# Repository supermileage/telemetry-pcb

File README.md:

# Telemetry PCB

Printed Circuit Board design for the Supermileage Telemetry Module. More information on its functionality can be found in the [firmware repo](https://github.com/supermileage/telemetry-firmware/tree/master).

The PCB is a 2-layer design, intended to be manufactured with 1oz copper. It was designed to be as small and as versatile as possible, to fit into tight spaces on multiple vehicles. The PCB features:

- Particle Boron Microcontroller with built-in LTE Connection
- LMS6DSO Accelerometer & Gyroscope
- 2x MAX31855K Thermocouple ICs with 2 Thermocouple inputs
- MCP2515 CAN Controller, TCAN332 CAN Transciever, 2x CAN ports
- Switchable TTL UART, RS232 UART (MAX3232), or optical UART (IF-D92)
- Connector for external i2c GPS module
- LEDs and button for monitoring & control

## Schematic Preview

## PCB Preview

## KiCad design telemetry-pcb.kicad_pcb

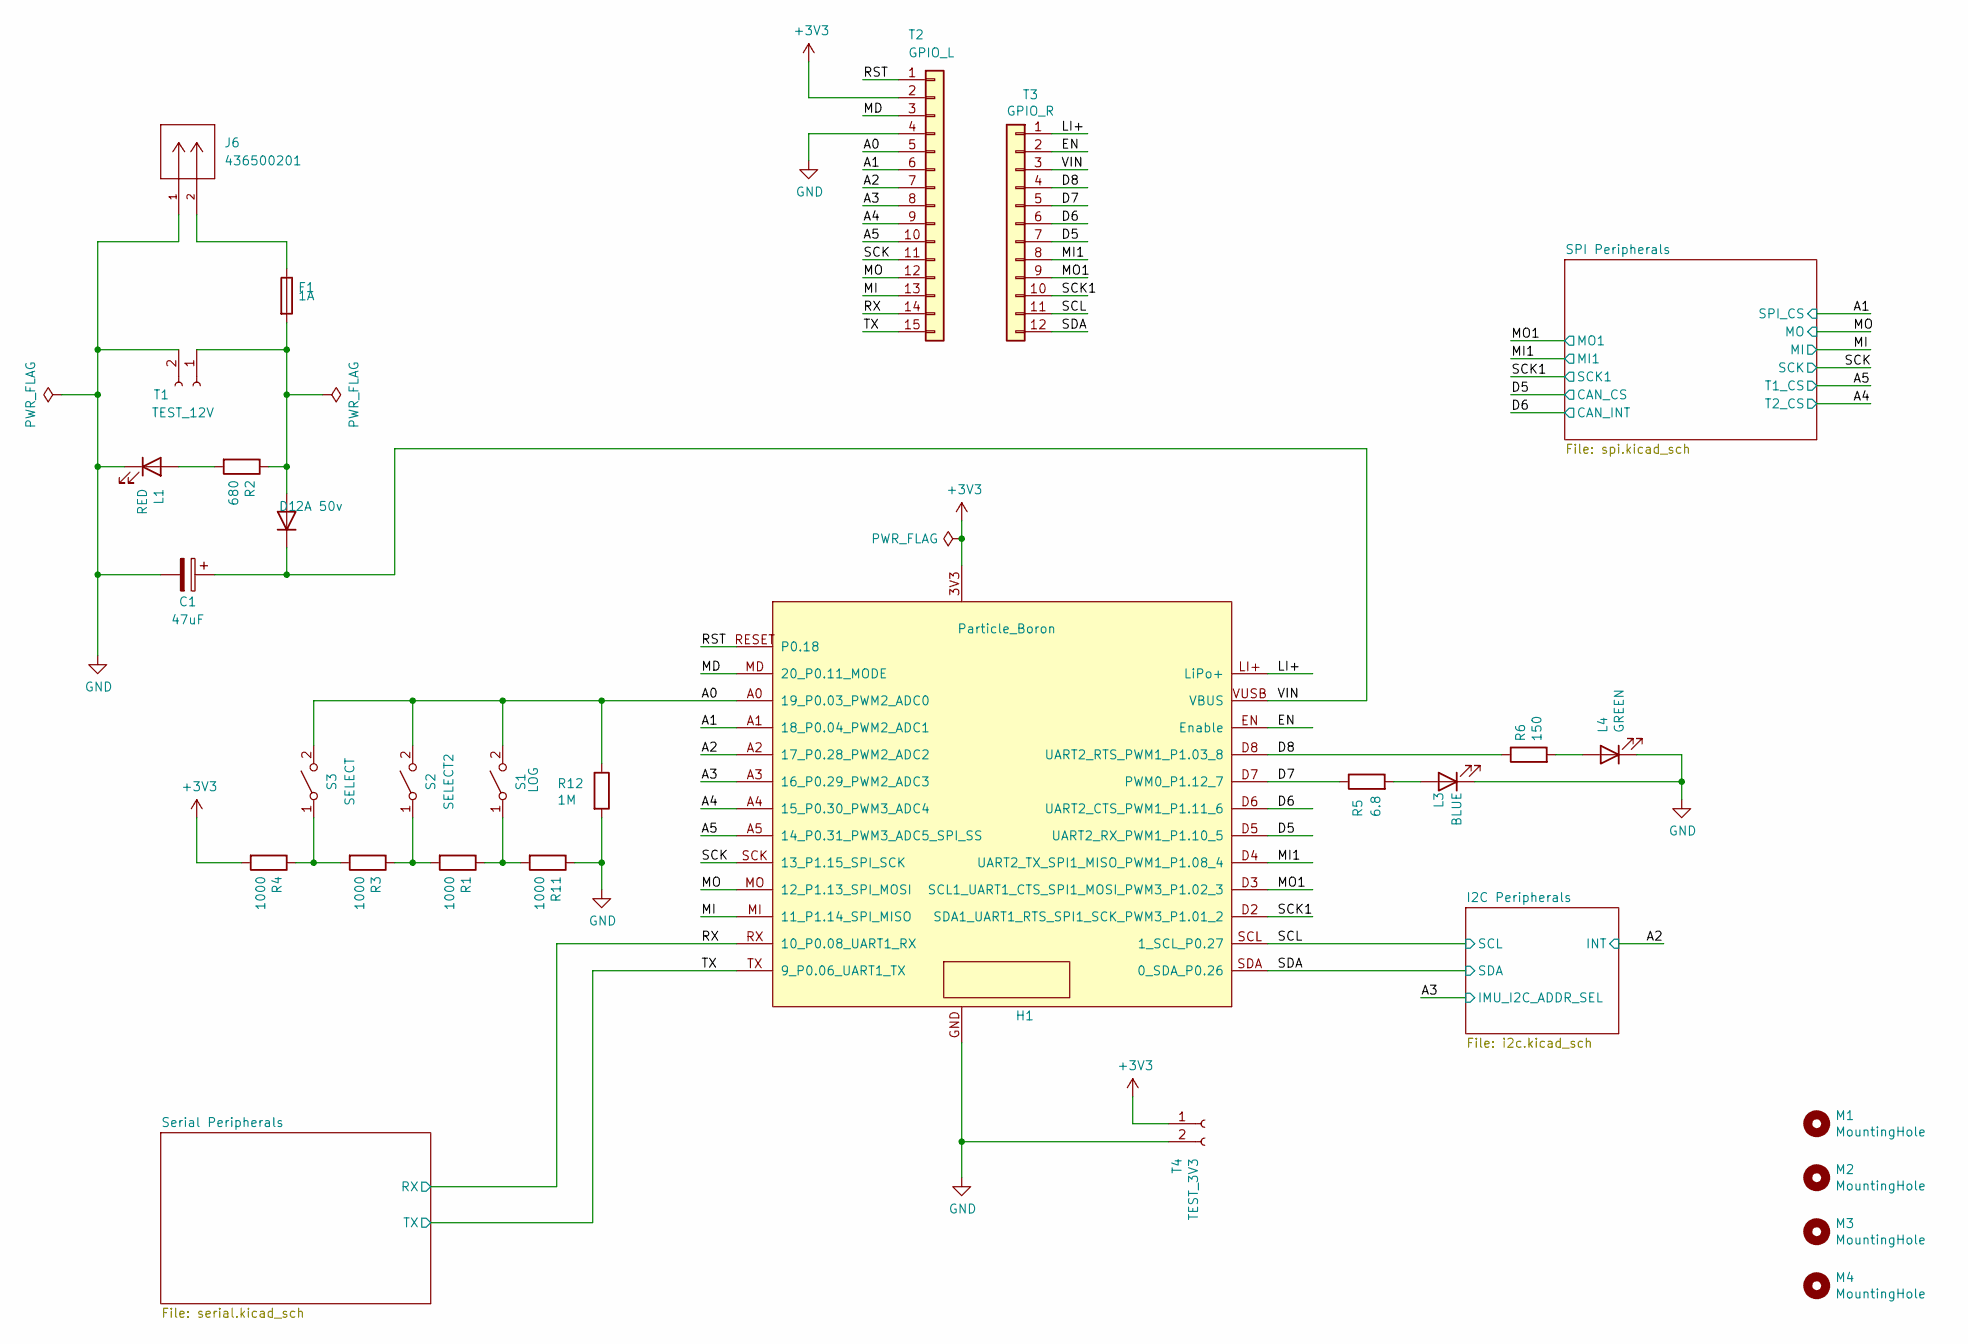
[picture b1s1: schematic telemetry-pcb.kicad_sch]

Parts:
C1: 47uF; CP_Elec_6.3x5.4
D1: 2A 50v; D_SMA
F1: 1A; 0154001.DRL
H1: Particle_Boron; Particle_boron
J6: 436500201; CONN_SD-43650-001_02_MOL; MANUFACTURER_PART_NUMBER 436500201
L1: RED; LED_0805_2012Metric
L3: BLUE; LED_0805_2012Metric
L4: GREEN; LED_0805_2012Metric
M1, M2, M3, M4: MountingHole; MountingHole_3.2mm_M3
R1, R3, R4, R11: 1000; R_0805_2012Metric
R2: 680; R_0805_2012Metric
R5: 6.8; R_0805_2012Metric
R6: 150; R_0805_2012Metric
R12: 1M; R_0805_2012Metric
S1: LOG; SW_PUSH_6mm_H13mm
S2: SELECT2; SW_PUSH_6mm_H13mm
S3: SELECT; SW_PUSH_6mm_H13mm
T1: TEST_12V; TestPoint_2Pads_Pitch2.54mm_Drill0.8mm
T2: GPIO_L; Boron_Pins_L
T3: GPIO_R; Boron_Pins_R
T4: TEST_3V3; TestPoint_2Pads_Pitch2.54mm_Drill0.8mm

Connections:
+3V3: H1.3V3, R4.2, T2.2, T4.1; also elsewhere on the board
/A0: H1.A0 (19_P0.03_PWM2_ADC0), R12.1, S1.2 (B), S2.2 (B), S3.2 (B), T2.5
/A1: H1.A1 (18_P0.04_PWM2_ADC1), T2.6; also elsewhere on the board
/A2: H1.A2 (17_P0.28_PWM2_ADC2), T2.7; also elsewhere on the board
/A3: H1.A3 (16_P0.29_PWM2_ADC3), T2.8; also elsewhere on the board
/A4: H1.A4 (15_P0.30_PWM3_ADC4), T2.9; also elsewhere on the board
/A5: H1.A5 (14_P0.31_PWM3_ADC5_SPI_SS), T2.10; also elsewhere on the board
/D5: H1.D5 (UART2_RX_PWM1_P1.10_5), T3.7; also elsewhere on the board
/D6: H1.D6 (UART2_CTS_PWM1_P1.11_6), T3.6; also elsewhere on the board
/D7: H1.D7 (PWM0_P1.12_7), R5.1, T3.5
/D8: H1.D8 (UART2_RTS_PWM1_P1.03_8), R6.1, T3.4
/EN: H1.EN (Enable), T3.2
/LI+: H1.LI+ (LiPo+), T3.1
/MD: H1.MD (20_P0.11_MODE), T2.3
/MI: H1.MI (11_P1.14_SPI_MISO), T2.13; also elsewhere on the board
/MI1: H1.D4 (UART2_TX_SPI1_MISO_PWM1_P1.08_4), T3.8; also elsewhere on the board
/MO: H1.MO (12_P1.13_SPI_MOSI), T2.12; also elsewhere on the board
/MO1: H1.D3 (SCL1_UART1_CTS_SPI1_MOSI_PWM3_P1.02_3), T3.9; also elsewhere on the board
/RST: H1.RESET (P0.18), T2.1
/RX: H1.RX (10_P0.08_UART1_RX), T2.14; also elsewhere on the board
/SCK: H1.SCK (13_P1.15_SPI_SCK), T2.11; also elsewhere on the board
/SCK1: H1.D2 (SDA1_UART1_RTS_SPI1_SCK_PWM3_P1.01_2), T3.10; also elsewhere on the board
/SCL: H1.SCL (1_SCL_P0.27), T3.11; also elsewhere on the board
/SDA: H1.SDA (0_SDA_P0.26), T3.12; also elsewhere on the board
/TX: H1.TX (9_P0.06_UART1_TX), T2.15; also elsewhere on the board
/VIN: C1.1, D1.1 (K), H1.VUSB (VBUS), T3.3
GND: C1.2, H1.GND, J6.1, L1.1 (K), L3.1 (K), L4.1 (K), R11.1, R12.2, T1.2, T2.4, T4.2; also elsewhere on the board
unnamed: D1.2 (A), F1.2, R2.1, T1.1
unnamed: F1.1, J6.2
unnamed: L1.2 (A), R2.2
unnamed: L3.2 (A), R5.2
unnamed: L4.2 (A), R6.2
unnamed: R1.1, R11.2, S1.1 (A)
unnamed: R1.2, R3.1, S2.1 (A)
unnamed: R3.2, R4.1, S3.1 (A)

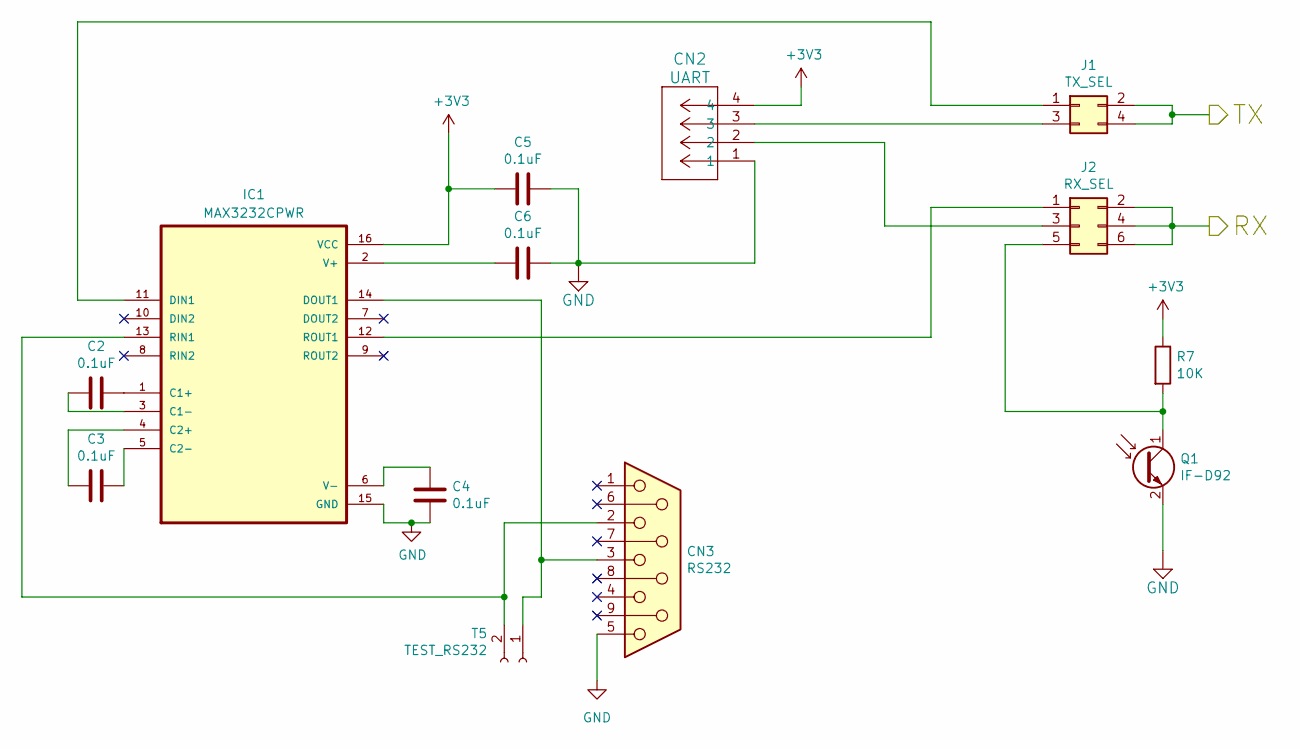
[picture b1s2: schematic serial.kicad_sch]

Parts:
C2, C3, C4, C5, C6: 0.1uF; C_0805_2012Metric
CN2: UART; CONN_SD-43650-001_04_MOL
CN3: RS232; DSUB-9_Female_Horizontal_P2.77x2.84mm_EdgePinOffset7.70mm_H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
IC1: MAX3232CPWR; TSSOP-16_4.4x5mm_P0.65mm
J1: TX_SEL; PinHeader_2x02_P2.54mm_Horizontal
J2: RX_SEL; PinHeader_2x03_P2.54mm_Horizontal
Q1: IF-D92
R7: 10K; R_0805_2012Metric
T5: TEST_RS232; TestPoint_2Pads_Pitch2.54mm_Drill0.8mm

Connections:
+3V3: C5.2, CN2.4, IC1.16 (VCC), R7.1; also elsewhere on the board
/RX: J2.2, J2.4, J2.6; also elsewhere on the board
/Serial Peripherals/RX_232: CN3.2, IC1.13 (RIN1), T5.2
/Serial Peripherals/TX_232: CN3.3, IC1.14 (DOUT1), T5.1
/TX: J1.2, J1.4; also elsewhere on the board
GND: C4.2, C5.1, C6.1, CN2.1, CN3.5, IC1.15 (GND), Q1.2 (E); also elsewhere on the board
unnamed: C2.1, IC1.1 (C1+)
unnamed: C2.2, IC1.3 (C1-)
unnamed: C3.2, IC1.4 (C2+)
unnamed: C3.1, IC1.5 (C2-)
unnamed: IC1.11 (DIN1), J1.1
unnamed: IC1.12 (ROUT1), J2.1
unnamed: C6.2, IC1.2 (V+)
unnamed: C4.1, IC1.6 (V-)
unnamed: CN2.3, J1.3
unnamed: CN2.2, J2.3
unnamed: J2.5, Q1.1 (C), R7.2

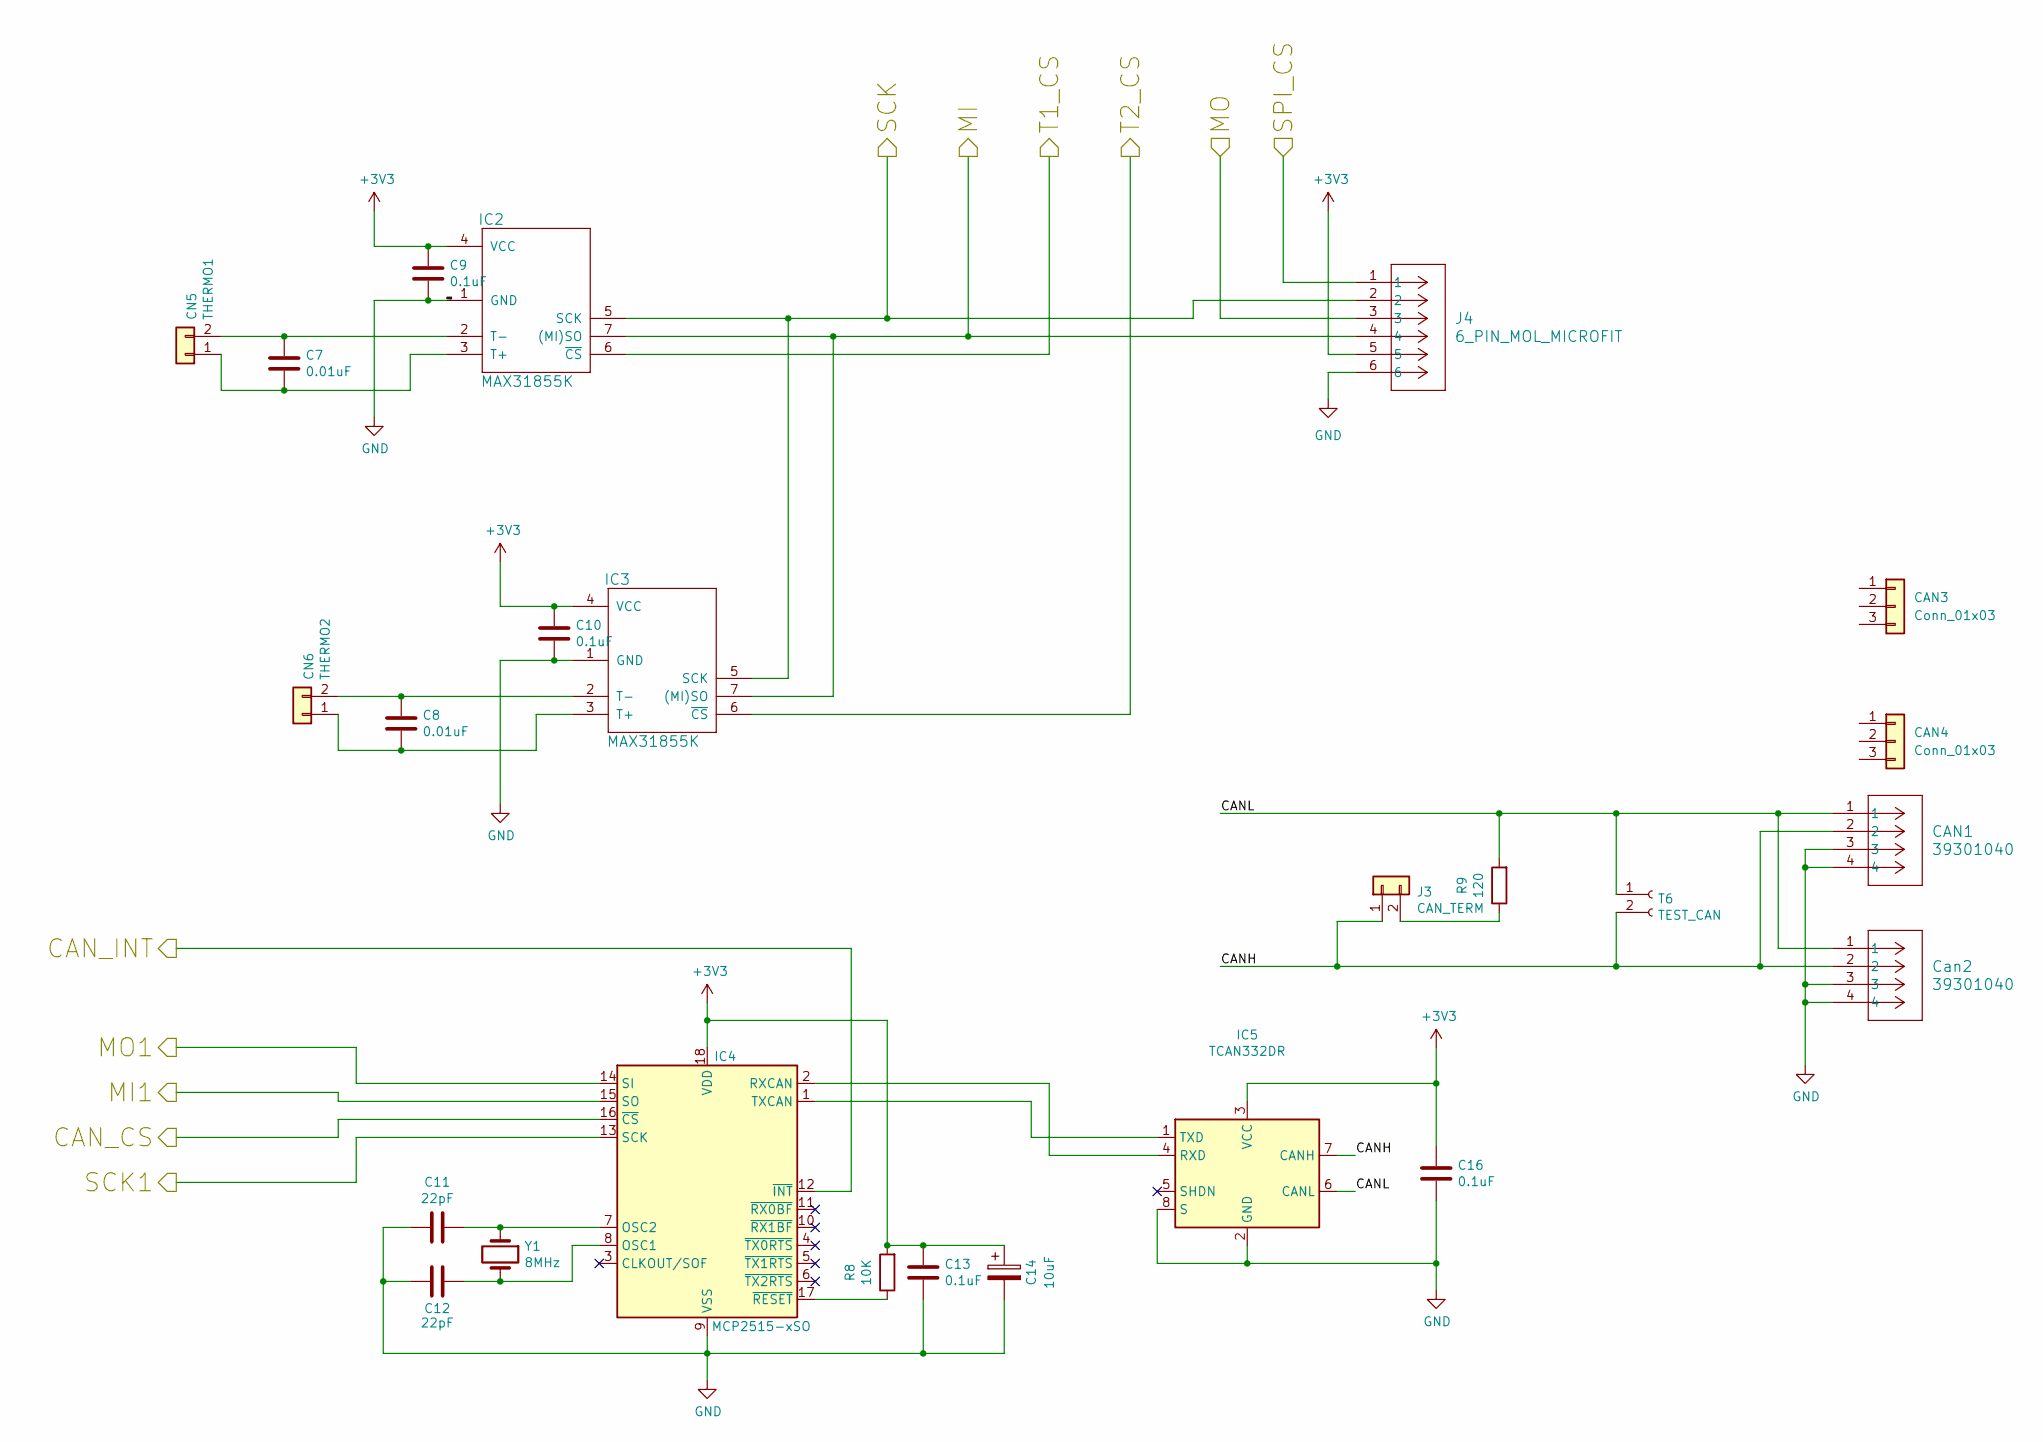
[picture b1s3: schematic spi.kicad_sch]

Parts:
C7, C8: 0.01uF; C_0805_2012Metric
C9, C10, C13, C16: 0.1uF; C_0805_2012Metric
C11, C12: 22pF; C_0805_2012Metric
C14: 10uF; C_1206_3216Metric
CAN1: 39301040; CONN_5569-04A_MOL
CAN3, CAN4: Conn_01x03; CONN_SD-43650-001_03_MOL
CN5: THERMO1; ScrewTermPlug1x02
CN6: THERMO2; ScrewTermPlug1x02
Can2: 39301040; CONN_5569-04A_MOL
IC2, IC3: MAX31855K; SOIC-8-1EP_3.9x4.9mm_P1.27mm_EP2.29x3mm
IC4: MCP2515-xSO; SOIC-18W_7.5x11.6mm_P1.27mm
IC5: TCAN332DR; SOIC-8-1EP_3.9x4.9mm_P1.27mm_EP2.29x3mm
J3: CAN_TERM; PinHeader_1x02_P2.54mm_Horizontal
J4: 6_PIN_MOL_MICROFIT; CONN_SD-43045-001_06_MOL
R8: 10K; R_0805_2012Metric
R9: 120; R_0805_2012Metric
T6: TEST_CAN; TestPoint_2Pads_Pitch2.54mm_Drill0.8mm
Y1: 8MHz; Crystal_SMD_HC49-SD

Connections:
+3V3: C9.1, C10.1, C13.2, C14.1, C16.2, IC2.4 (VCC), IC3.4 (VCC), IC4.18 (VDD), IC5.3 (VCC), J4.5, R8.2; also elsewhere on the board
/A1: J4.1; also elsewhere on the board
/A4: IC3.6 (~CS); also elsewhere on the board
/A5: IC2.6 (~CS); also elsewhere on the board
/D5: IC4.16 (~CS); also elsewhere on the board
/D6: IC4.12 (~INT); also elsewhere on the board
/MI: IC2.7 ((MI)SO), IC3.7 ((MI)SO), J4.4; also elsewhere on the board
/MI1: IC4.15 (SO); also elsewhere on the board
/MO: J4.3; also elsewhere on the board
/MO1: IC4.14 (SI); also elsewhere on the board
/SCK: IC2.5 (SCK), IC3.5 (SCK), J4.2; also elsewhere on the board
/SCK1: IC4.13 (SCK); also elsewhere on the board
/SPI Peripherals/CANH: CAN1.2, Can2.2, IC5.7 (CANH), J3.1, T6.2; also elsewhere on the board
/SPI Peripherals/CANL: CAN1.1, Can2.1, IC5.6 (CANL), R9.2, T6.1; also elsewhere on the board
GND: C9.2, C10.2, C11.2, C12.2, C13.1, C14.2, C16.1, CAN1.3, CAN1.4, Can2.3, Can2.4, IC2.1 (GND), IC3.1 (GND), IC4.9 (VSS), IC5.2 (GND), IC5.8 (S), J4.6; also elsewhere on the board
unnamed: C7.2, CN5.1, IC2.3 (T+)
unnamed: C7.1, CN5.2, IC2.2 (T-)
unnamed: C8.2, CN6.1, IC3.3 (T+)
unnamed: C8.1, CN6.2, IC3.2 (T-)
unnamed: C12.1, IC4.8 (OSC1), Y1.2
unnamed: C11.1, IC4.7 (OSC2), Y1.1
unnamed: IC4.2 (RXCAN), IC5.4 (RXD)
unnamed: IC4.1 (TXCAN), IC5.1 (TXD)
unnamed: IC4.17 (~RESET), R8.1
unnamed: J3.2, R9.1

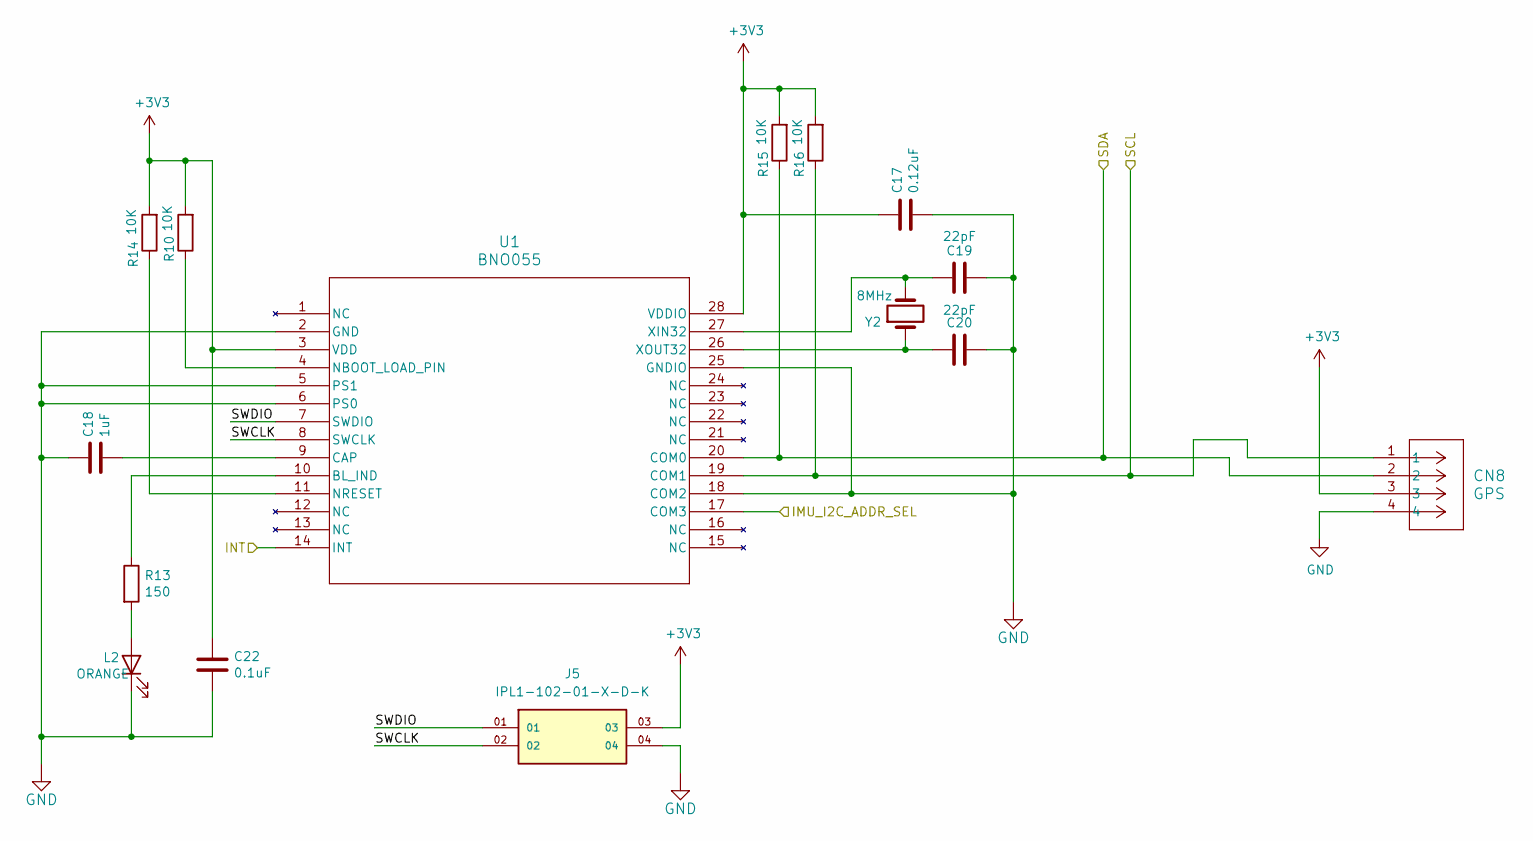
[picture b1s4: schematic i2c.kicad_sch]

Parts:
C17: 0.12uF; C_0805_2012Metric
C18: 1uF; C_1206_3216Metric_Pad1.33x1.80mm_HandSolder
C19, C20: 22pF; C_0805_2012Metric
C22: 0.1uF; C_0805_2012Metric
CN8: GPS; CONN_SD-43650-001_04_MOL
J5: IPL1-102-01-X-D-K; SAMTEC_IPL1-102-01-X-D-K; PARTREV E
L2: ORANGE; LED_0805_2012Metric
R10, R14, R15, R16: 10K; R_0805_2012Metric
R13: 150; R_0805_2012Metric
U1: BNO055; QFN_BNO055_BOS
Y2: 8MHz; XTAL_ABS07-32.768KHZ-T

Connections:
+3V3: C17.1, C22.1, CN8.3, J5.03, R10.2, R14.2, R15.2, R16.2, U1.3 (VDD), U1.28 (VDDIO); also elsewhere on the board
/A2: U1.14 (INT); also elsewhere on the board
/A3: U1.17 (COM3); also elsewhere on the board
/I2C Peripherals/SWCLK: J5.02, U1.8 (SWCLK)
/I2C Peripherals/SWDIO: J5.01, U1.7 (SWDIO)
/SCL: CN8.1, R16.1, U1.19 (COM1); also elsewhere on the board
/SDA: CN8.2, R15.1, U1.20 (COM0); also elsewhere on the board
GND: C17.2, C18.1, C19.2, C20.2, C22.2, CN8.4, J5.04, L2.1 (K), U1.2 (GND), U1.5 (PS1), U1.6 (PS0), U1.18 (COM2), U1.25 (GNDIO); also elsewhere on the board
unnamed: L2.2 (A), R13.2
unnamed: R13.1, U1.10 (BL_IND)
unnamed: C18.2, U1.9 (CAP)
unnamed: R10.1, U1.4 (NBOOT_LOAD_PIN)
unnamed: R14.1, U1.11 (NRESET)
unnamed: C19.1, U1.27 (XIN32), Y2.2
unnamed: C20.1, U1.26 (XOUT32), Y2.1

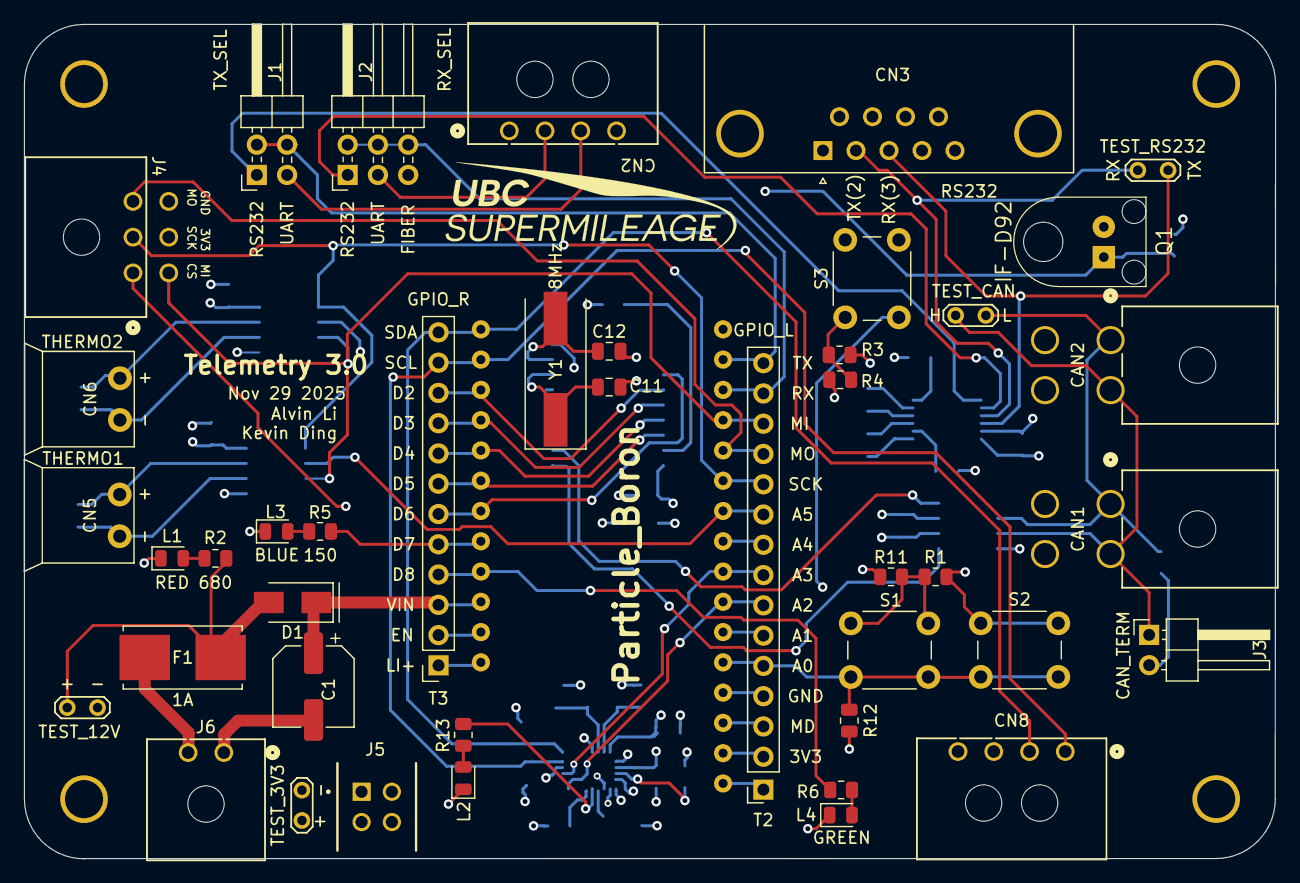
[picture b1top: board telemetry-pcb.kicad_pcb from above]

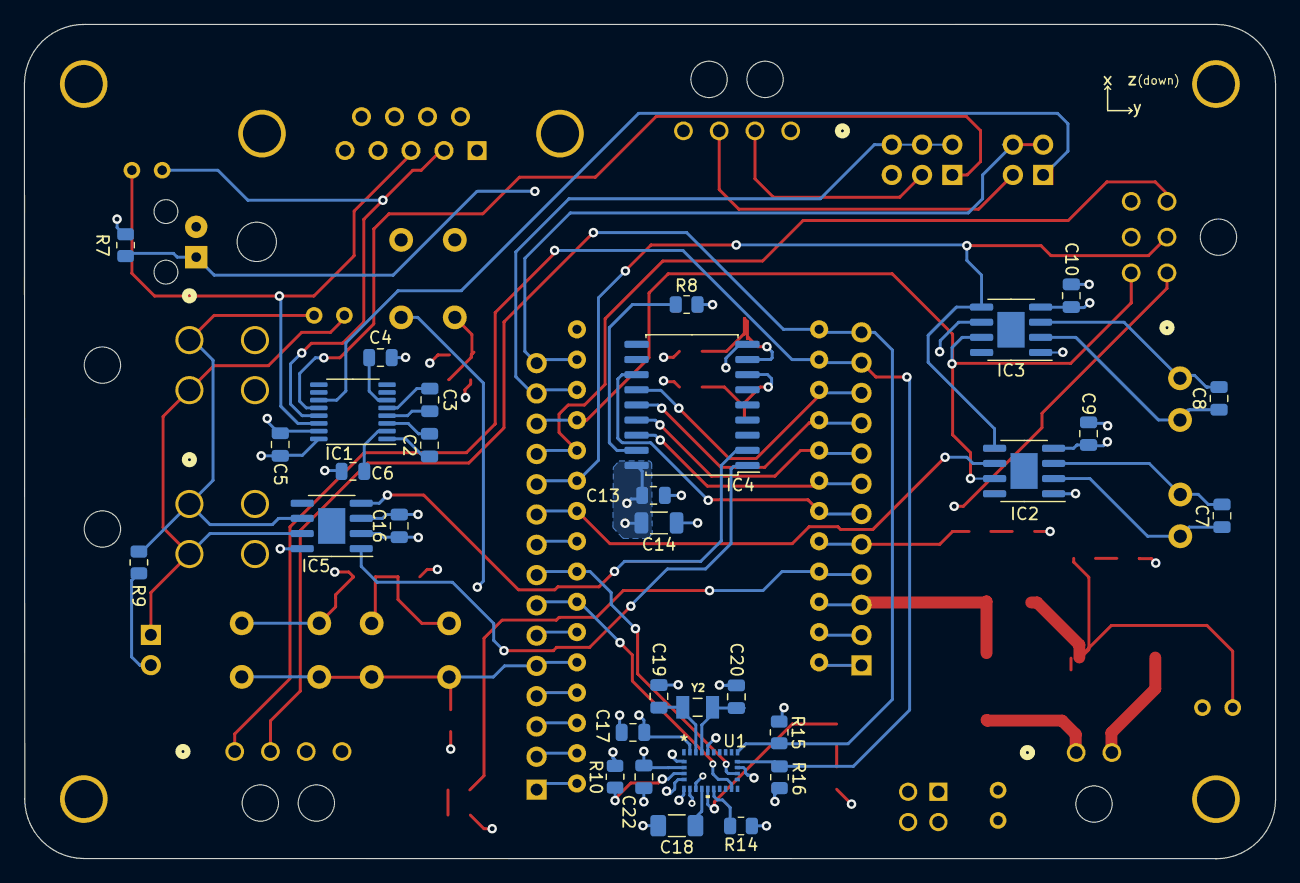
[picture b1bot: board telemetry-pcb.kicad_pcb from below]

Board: 4 copper layers, 105.0 x 70.0 mm, 78 parts (31 on the bottom side), 69 nets.

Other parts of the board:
CAN2: 39301040; CONN_5569-04A_MOL

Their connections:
/SPI Peripherals/CANH: CAN2.2; also elsewhere on the board
/SPI Peripherals/CANL: CAN2.1; also elsewhere on the board
GND: CAN2.3, CAN2.4; also elsewhere on the board

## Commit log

2021-01-20 added Electron pinout
2021-01-20 added gitignore
2021-01-22 finished first draft of Electron schematic
2021-01-22 uploaded the correct project this time
2021-01-23 replaced headers with screw terminals, placed 12v off board
2021-01-27 finished schematic with 12v off-board input and outputs as specified on Notion
2021-01-27 added fan connector
2021-01-27 added first draft of BOM
2021-01-27 fixed design rule violations and added input diode
2021-01-27 removed trailing wire under R1
2021-01-30 finalized schematic based on review feedback
2021-02-01 laid out all components and got most footprints imported
2021-02-03 finished first draft of PCB
2021-02-03 cleaned up repo
2021-02-05 added references to silkscreen and fixed Molex SL footprint soldermask
2021-02-06 fixed molex sl 2pos footprint
2021-02-13 final version for Particle Electron
2021-02-15 finished first draft of schematic with Boron
2021-02-15 finished first draft of schematic for Boron
2021-02-15 finished footprint selection, placement, and silkscreen.
2021-02-27 finished PCB routing
2021-03-10 updated PCB to fix two errors: TX/RX were switched on DB9 jack, and SPI was not connected to MAX31855 ICs
2021-03-20 made some final changes to PCB and BOM
2021-05-08 Adding PCBway fab files
2021-09-08 revert before everything was messed up
2021-09-08 fixed merge issues
2021-09-09 small changes and gerber file for JLPCB
2021-09-10 added JLPCB gerber files
2021-09-17 updated BOM with some missing items + external connectors
2021-11-02 started on 1.1 redesign, schematic is done and PCB has just been started.
2022-02-25 finished schematic and PCB layout for 1.1 board
2022-02-25 routed all
2022-03-03 removes one power port, changes CAN switch to jumper
2022-03-03 updates PCB to move serial headers next to serial ports, CAN header next to CAN ports
2022-03-04 Updates BOM
2022-03-04 added bottom silkscreen logo, date, and names
2022-03-04 deleted extraneous footprints
2022-03-08 Shrinks board and removes GPS. Replaces GPS with Qwiic connector for off-board GPS
2022-03-14 changes CAN ports to 3 pin, Thermocouple ports to 2 pin
2022-07-29 minor changes to serial port - update rs232 connector and delete GND connection
2022-08-02 fixes optical receiver wiring and changes GPS connector to JST GH
2022-08-04 some more small changes from design review
2022-08-09 2-0 complete
2022-08-10 adds gerber files
2022-09-10 Some small changes
2022-11-19 fixes button issue
2022-11-19 fixed power flag in schematic causing error
2022-11-20 creates gerber files
2022-11-20 updates gerber files to kicad standards, changes version number and date on silkscreen
2023-08-22 updates readme and adds photos
2025-10-25 3.0 Preliminary Changes
2025-11-08 hello
2025-11-22 Backup
2025-12-02 Completed PCB routing
    new footprints added to Footprints folder, added I2C peripherals page.
2025-12-09 added logo
2025-12-09 review me
2025-12-09 Updated PCB after design review
2026-01-05 All review changes complete, except update CAN connector
2026-01-10 routing update
2026-01-11 connector changes
2026-01-14 more changes

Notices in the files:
parts and their libraries:
Copyright 2021 Accelerated Designs. All rights reserved.
